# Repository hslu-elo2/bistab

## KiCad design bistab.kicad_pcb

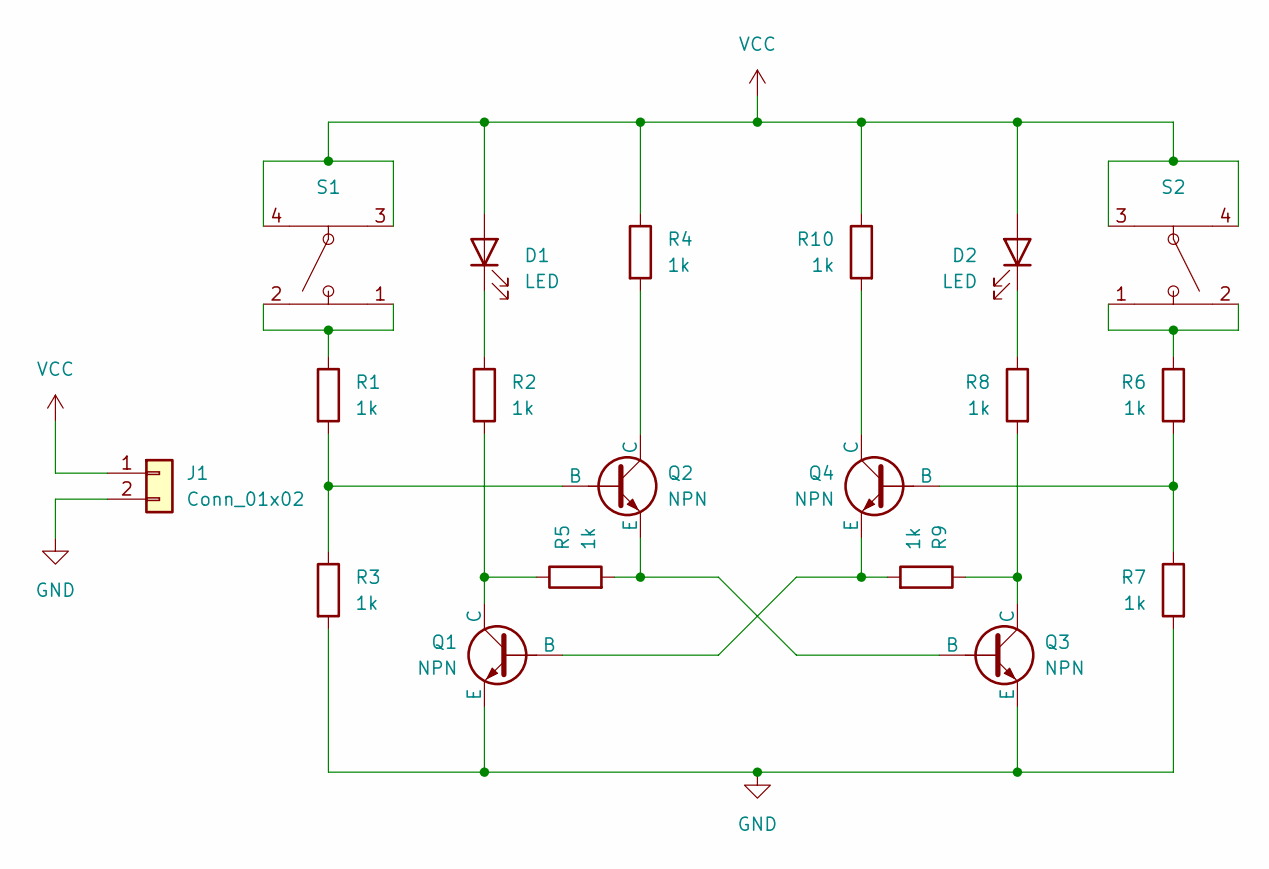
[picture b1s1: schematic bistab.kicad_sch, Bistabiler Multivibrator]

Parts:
D1, D2: LED; LED_0805_2012Metric
J1: Conn_01x02; PinHeader_1x02_P2.54mm_Vertical
Q1, Q2, Q3, Q4: NPN; SOT-23-3
R1, R2, R3, R4, R5, R6, R7, R8, R9, R10: 1k; R_0805_2012Metric
S1, S2: PTS645SM43SMTR92 LFS

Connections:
GND: J1.2, Q1.3 (E), Q3.3 (E), R3.2, R7.2
unnamed: D1.1 (K), R2.1
unnamed: D2.1 (K), R8.1
unnamed: Q1.2 (B), Q4.3 (E), R9.2
unnamed: Q1.1 (C), R2.2, R5.1
unnamed: Q2.2 (B), R1.2, R3.1
unnamed: Q2.1 (C), R4.2
unnamed: Q2.3 (E), Q3.2 (B), R5.2
unnamed: Q3.1 (C), R8.2, R9.1
unnamed: Q4.2 (B), R6.2, R7.1
unnamed: Q4.1 (C), R10.2
unnamed: R1.1, S1.1, S1.2
unnamed: R6.1, S2.1, S2.2
VCC: D1.2 (A), D2.2 (A), J1.1, R4.1, R10.1, S1.3, S1.4, S2.3, S2.4

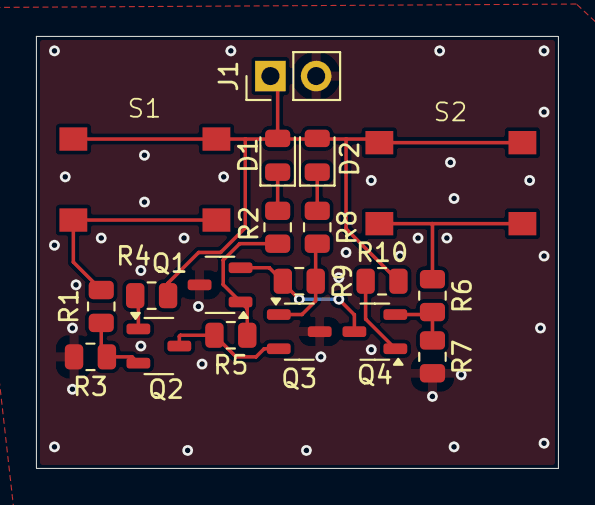
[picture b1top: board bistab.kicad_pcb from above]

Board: 2 copper layers, 29.0 x 24.0 mm, 19 parts (0 on the bottom side), 14 nets.

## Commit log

2024-10-09 added footprint assignment
2024-10-09 add component placement
2024-10-09 add layout
